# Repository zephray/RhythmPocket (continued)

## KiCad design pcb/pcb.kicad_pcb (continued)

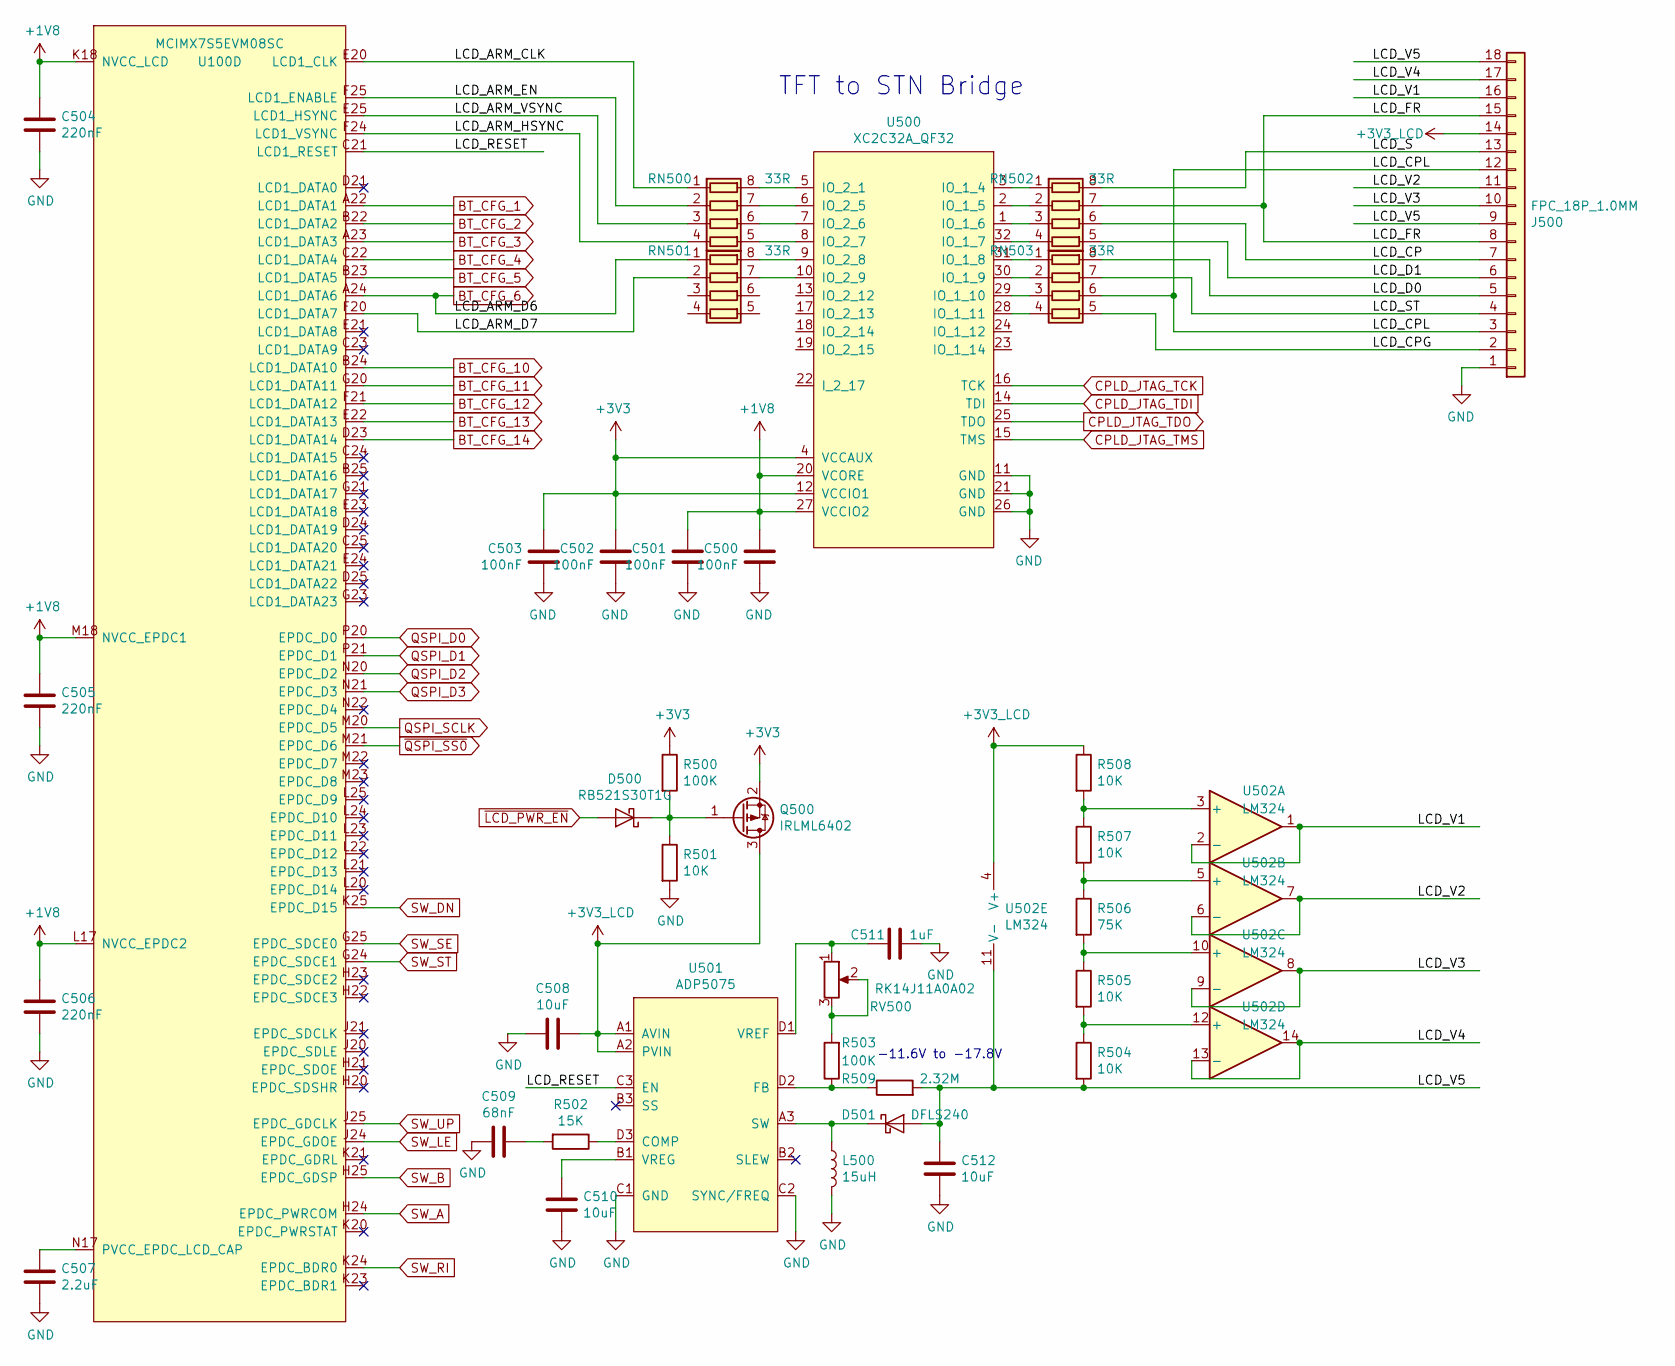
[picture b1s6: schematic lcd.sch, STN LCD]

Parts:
C500, C501, C502, C503: 100nF; C_0402_1005Metric
C504, C505, C506: 220nF; C_0402_1005Metric
C507: 2.2uF; C_0402_1005Metric
C508, C510, C512: 10uF; C_0603_1608Metric
C509: 68nF; C_0402_1005Metric
C511: 1uF; C_0402_1005Metric
D500: RB521S30T1G; D_SOD-523
D501: DFLS240; D_SOD-123
J500: FPC_18P_1.0MM; TE_1-84953-8_1x18-1MP_P1.0mm_Horizontal
L500: 15uH; L_Vishay_IHLP-1212
Q500: IRLML6402; SOT-23
R500, R503: 100K; R_0603_1608Metric
R501, R504, R505, R507, R508: 10K; R_0603_1608Metric
R502: 15K; R_0603_1608Metric
R506: 75K; R_0603_1608Metric
R509: 2.32M; R_0603_1608Metric
RN500, RN501, RN502, RN503: 33R; R_Array_Convex_4x0402
RV500: RK14J11A0A02; Potentiometer_RK14J
U100: MCIMX7S5EVM08SC; BGA-541_25x25_19.0x19.0mm
U500: XC2C32A_QF32; QFN-32-1EP_5x5mm_P0.5mm_EP3.1x3.1mm
U501: ADP5075; WLCSP-12_3x4
U502: LM324; SOIC-16_3.9x9.9mm_P1.27mm

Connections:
+1V8: C500.1, C501.1, C504.1, C505.1, C506.1, U100.K18 (NVCC_LCD), U100.L17 (NVCC_EPDC2), U100.M18 (NVCC_EPDC1), U500.20 (VCORE), U500.27 (VCCIO2); also elsewhere on the board
+3V3: C502.1, C503.1, Q500.2 (S), R500.1, U500.4 (VCCAUX), U500.12 (VCCIO1); also elsewhere on the board
+3V3_LCD: C508.1, J500.14, Q500.3 (D), R508.1, U501.A1 (AVIN), U501.A2 (PVIN), U502.4 (V+)
/lcd/LCD_ARM_CLK: RN500.1 (R1.1), U100.E20 (LCD1_CLK)
/lcd/LCD_ARM_D7: RN501.2 (R2.1), U100.F20 (LCD1_DATA7)
/lcd/LCD_ARM_EN: RN500.2 (R2.1), U100.F25 (LCD1_ENABLE)
/lcd/LCD_ARM_HSYNC: RN500.4 (R4.1), U100.F24 (LCD1_VSYNC)
/lcd/LCD_ARM_VSYNC: RN500.3 (R3.1), U100.E25 (LCD1_HSYNC)
/lcd/LCD_CP: J500.7, RN502.6 (R3.2)
/lcd/LCD_CPG: J500.2, RN503.5 (R4.2)
/lcd/LCD_CPL: J500.3, J500.12, RN503.6 (R3.2)
/lcd/LCD_D0: J500.5, RN503.8 (R1.2)
/lcd/LCD_D1: J500.6, RN502.5 (R4.2)
/lcd/LCD_FR: J500.8, J500.15, RN502.7 (R2.2)
/lcd/LCD_RESET: U100.C21 (LCD1_RESET), U501.C3 (EN)
/lcd/LCD_S: J500.13, RN502.8 (R1.2)
/lcd/LCD_ST: J500.4, RN503.7 (R2.2)
/lcd/LCD_V1: J500.16, U502.1, U502.2 (-)
/lcd/LCD_V2: J500.11, U502.6 (-), U502.7
/lcd/LCD_V3: J500.10, U502.8, U502.9 (-)
/lcd/LCD_V4: J500.17, U502.13 (-), U502.14
/lcd/LCD_V5: C512.2, D501.2 (A), J500.9, J500.18, R504.2, R509.2, U502.11 (V-)
BT_CFG_1: U100.A22 (LCD1_DATA1); also elsewhere on the board
BT_CFG_2: U100.B22 (LCD1_DATA2); also elsewhere on the board
BT_CFG_3: U100.A23 (LCD1_DATA3); also elsewhere on the board
BT_CFG_4: U100.C22 (LCD1_DATA4); also elsewhere on the board
BT_CFG_5: U100.B23 (LCD1_DATA5); also elsewhere on the board
BT_CFG_6: RN501.1 (R1.1), U100.A24 (LCD1_DATA6); also elsewhere on the board
BT_CFG_10: U100.B24 (LCD1_DATA10); also elsewhere on the board
BT_CFG_11: U100.G20 (LCD1_DATA11); also elsewhere on the board
BT_CFG_12: U100.F21 (LCD1_DATA12); also elsewhere on the board
BT_CFG_13: U100.E22 (LCD1_DATA13); also elsewhere on the board
BT_CFG_14: U100.D23 (LCD1_DATA14); also elsewhere on the board
CPLD_JTAG_TCK: U500.16 (TCK); also elsewhere on the board
CPLD_JTAG_TDI: U500.14 (TDI); also elsewhere on the board
CPLD_JTAG_TDO: U500.25 (TDO); also elsewhere on the board
CPLD_JTAG_TMS: U500.15 (TMS); also elsewhere on the board
GND: C500.2, C501.2, C502.2, C503.2, C504.2, C505.2, C506.2, C507.2, C508.2, C509.2, C510.2, C511.1, C512.1, J500.1, L500.2, R501.2, U500.11 (GND), U500.21 (GND), U500.26 (GND), U501.C1 (GND), U501.C2 (SYNC/FREQ); also elsewhere on the board
unnamed: C507.1, U100.N17 (PVCC_EPDC_LCD_CAP)
unnamed: C509.1, R502.2
unnamed: C510.1, U501.B1 (VREG)
unnamed: C511.2, RV500.1, U501.D1 (VREF)
unnamed: D500.1 (K), Q500.1 (G), R500.2, R501.1
unnamed: D501.1 (K), L500.1, U501.A3 (SW)
unnamed: R502.1, U501.D3 (COMP)
unnamed: R503.1, R509.1, U501.D2 (FB)
unnamed: R503.2, RV500.2, RV500.3
unnamed: R504.1, R505.2, U502.12 (+)
unnamed: R505.1, R506.2, U502.10 (+)
unnamed: R506.1, R507.2, U502.5 (+)
unnamed: R507.1, R508.2, U502.3 (+)
unnamed: RN500.5 (R4.2), U500.8 (IO_2_7)
unnamed: RN500.6 (R3.2), U500.7 (IO_2_6)
unnamed: RN500.7 (R2.2), U500.6 (IO_2_5)
unnamed: RN500.8 (R1.2), U500.5 (IO_2_1)
unnamed: RN501.7 (R2.2), U500.10 (IO_2_9)
unnamed: RN501.8 (R1.2), U500.9 (IO_2_8)
unnamed: RN502.1 (R1.1), U500.3 (IO_1_4)
unnamed: RN502.2 (R2.1), U500.2 (IO_1_5)
unnamed: RN502.3 (R3.1), U500.1 (IO_1_6)
unnamed: RN502.4 (R4.1), U500.32 (IO_1_7)
unnamed: RN503.1 (R1.1), U500.31 (IO_1_8)
unnamed: RN503.2 (R2.1), U500.30 (IO_1_9)
unnamed: RN503.3 (R3.1), U500.29 (IO_1_10)
unnamed: RN503.4 (R4.1), U500.28 (IO_1_11)
QSPI_D0: U100.P20 (EPDC_D0); also elsewhere on the board
QSPI_D1: U100.P21 (EPDC_D1); also elsewhere on the board
QSPI_D2: U100.N20 (EPDC_D2); also elsewhere on the board
QSPI_D3: U100.N21 (EPDC_D3); also elsewhere on the board
QSPI_SCLK: U100.M20 (EPDC_D5); also elsewhere on the board
SW_A: U100.H24 (EPDC_PWRCOM); also elsewhere on the board
SW_B: U100.H25 (EPDC_GDSP); also elsewhere on the board
SW_DN: U100.K25 (EPDC_D15); also elsewhere on the board
SW_LE: U100.J24 (EPDC_GDOE); also elsewhere on the board
SW_RI: U100.K24 (EPDC_BDR0); also elsewhere on the board
SW_SE: U100.G25 (EPDC_SDCE0); also elsewhere on the board
SW_ST: U100.G24 (EPDC_SDCE1); also elsewhere on the board
SW_UP: U100.J25 (EPDC_GDCLK); also elsewhere on the board
~LCD_PWR_EN: D500.2 (A); also elsewhere on the board
~QSPI_SS0: U100.M21 (EPDC_D6); also elsewhere on the board

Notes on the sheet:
TFT to STN Bridge
-11.6V to -17.8V

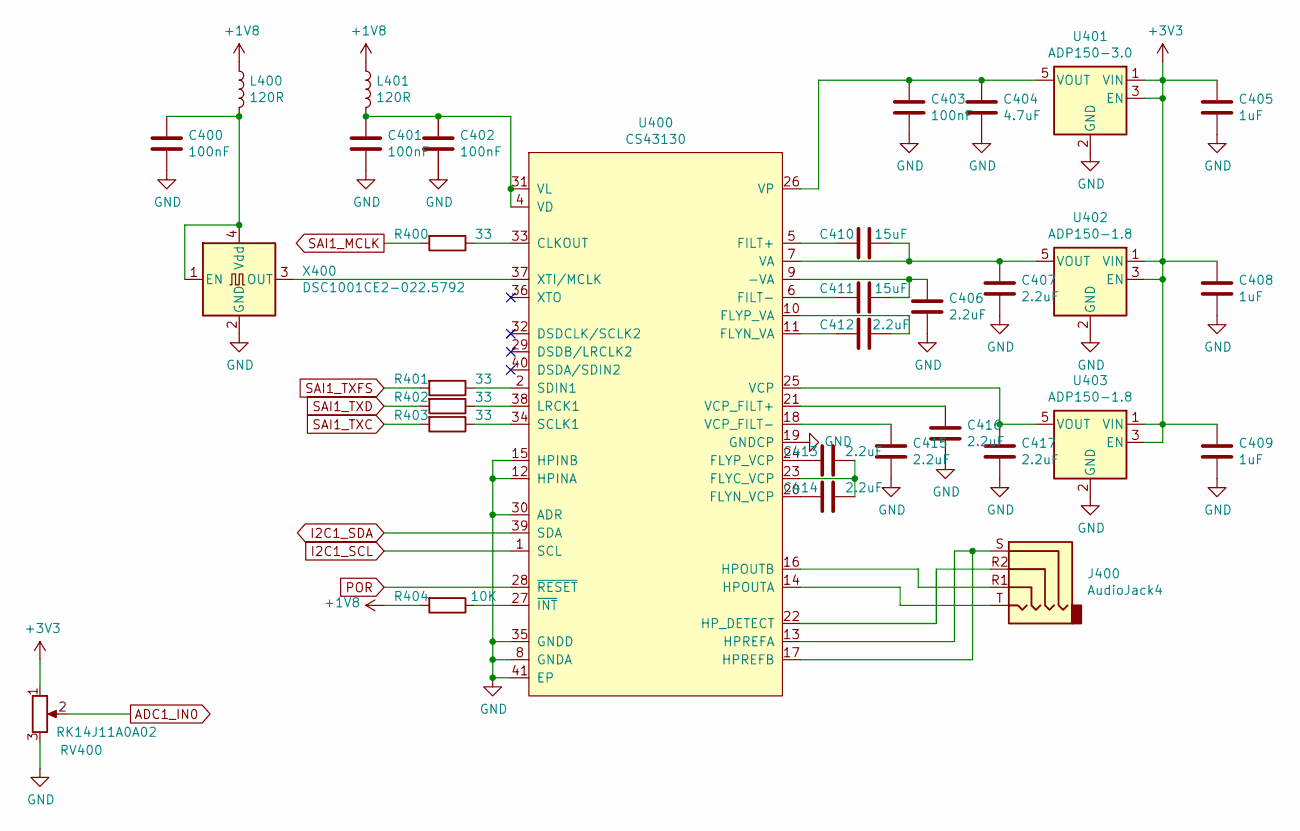
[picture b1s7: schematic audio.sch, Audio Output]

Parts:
C400, C401, C402, C403: 100nF; C_0402_1005Metric
C404: 4.7uF; C_0603_1608Metric
C405, C408, C409: 1uF; C_0402_1005Metric
C406, C407, C412, C413, C414, C415, C416, C417: 2.2uF; C_0402_1005Metric
C410, C411: 15uF; C_0603_1608Metric
J400: AudioJack4; Jack_3.5mm_PJ320D_Horizontal
L400, L401: 120R; L_0603_1608Metric
R400, R401, R402, R403: 33; R_0603_1608Metric
R404: 10K; R_0603_1608Metric
RV400: RK14J11A0A02; Potentiometer_RK14J
U400: CS43130; QFN-40-1EP_5x5mm_P0.4mm_EP3.6x3.6mm_ThermalVias
U401: ADP150-3.0; SOT-23-5
U402, U403: ADP150-1.8; SOT-23-5
X400: DSC1001CE2-022.5792; Oscillator_SMD_Abracon_ASE-4Pin_3.2x2.5mm

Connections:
+1V8: L400.1, L401.1, R404.2; also elsewhere on the board
+3V3: C405.1, C408.1, C409.1, RV400.1, U401.1 (VIN), U401.3 (EN), U402.1 (VIN), U402.3 (EN), U403.1 (VIN), U403.3 (EN); also elsewhere on the board
ADC1_IN0: RV400.2; also elsewhere on the board
GND: C400.2, C401.2, C402.2, C403.2, C404.2, C405.2, C406.2, C407.2, C408.2, C409.2, C415.2, C416.2, C417.2, RV400.3, U400.8 (GNDA), U400.12 (HPINA), U400.15 (HPINB), U400.19 (GNDCP), U400.30 (ADR), U400.35 (GNDD), U400.41 (EP), U401.2 (GND), U402.2 (GND), U403.2 (GND), X400.2 (GND); also elsewhere on the board
I2C1_SCL: U400.1 (SCL); also elsewhere on the board
I2C1_SDA: U400.39 (SDA); also elsewhere on the board
unnamed: C400.1, L400.2, X400.1 (EN), X400.4 (Vdd)
unnamed: C401.1, C402.1, L401.2, U400.4 (VD), U400.31 (VL)
unnamed: C403.1, C404.1, U400.26 (VP), U401.5 (VOUT)
unnamed: C406.1, C411.1, U400.9 (-VA)
unnamed: C407.1, C410.1, U400.7 (VA), U402.5 (VOUT)
unnamed: C410.2, U400.5 (FILT+)
unnamed: C411.2, U400.6 (FILT-)
unnamed: C412.1, U400.10 (FLYP_VA)
unnamed: C412.2, U400.11 (FLYN_VA)
unnamed: C413.1, C414.1, U400.23 (FLYC_VCP)
unnamed: C413.2, U400.24 (FLYP_VCP)
unnamed: C414.2, U400.20 (FLYN_VCP)
unnamed: C415.1, U400.18 (VCP_FILT-)
unnamed: C416.1, U400.21 (VCP_FILT+)
unnamed: C417.1, U400.25 (VCP), U403.5 (VOUT)
unnamed: J400.R1, U400.16 (HPOUTB)
unnamed: J400.R2, U400.22 (HP_DETECT)
unnamed: J400.S, U400.13 (HPREFA), U400.17 (HPREFB)
unnamed: J400.T, U400.14 (HPOUTA)
unnamed: R400.1, U400.33 (CLKOUT)
unnamed: R401.1, U400.2 (SDIN1)
unnamed: R402.1, U400.38 (LRCK1)
unnamed: R403.1, U400.34 (SCLK1)
unnamed: R404.1, U400.27 (~INT)
unnamed: U400.37 (XTI/MCLK), X400.3 (OUT)
POR: U400.28 (~RESET); also elsewhere on the board
SAI1_MCLK: R400.2; also elsewhere on the board
SAI1_TXC: R403.2; also elsewhere on the board
SAI1_TXD: R402.2; also elsewhere on the board
SAI1_TXFS: R401.2; also elsewhere on the board

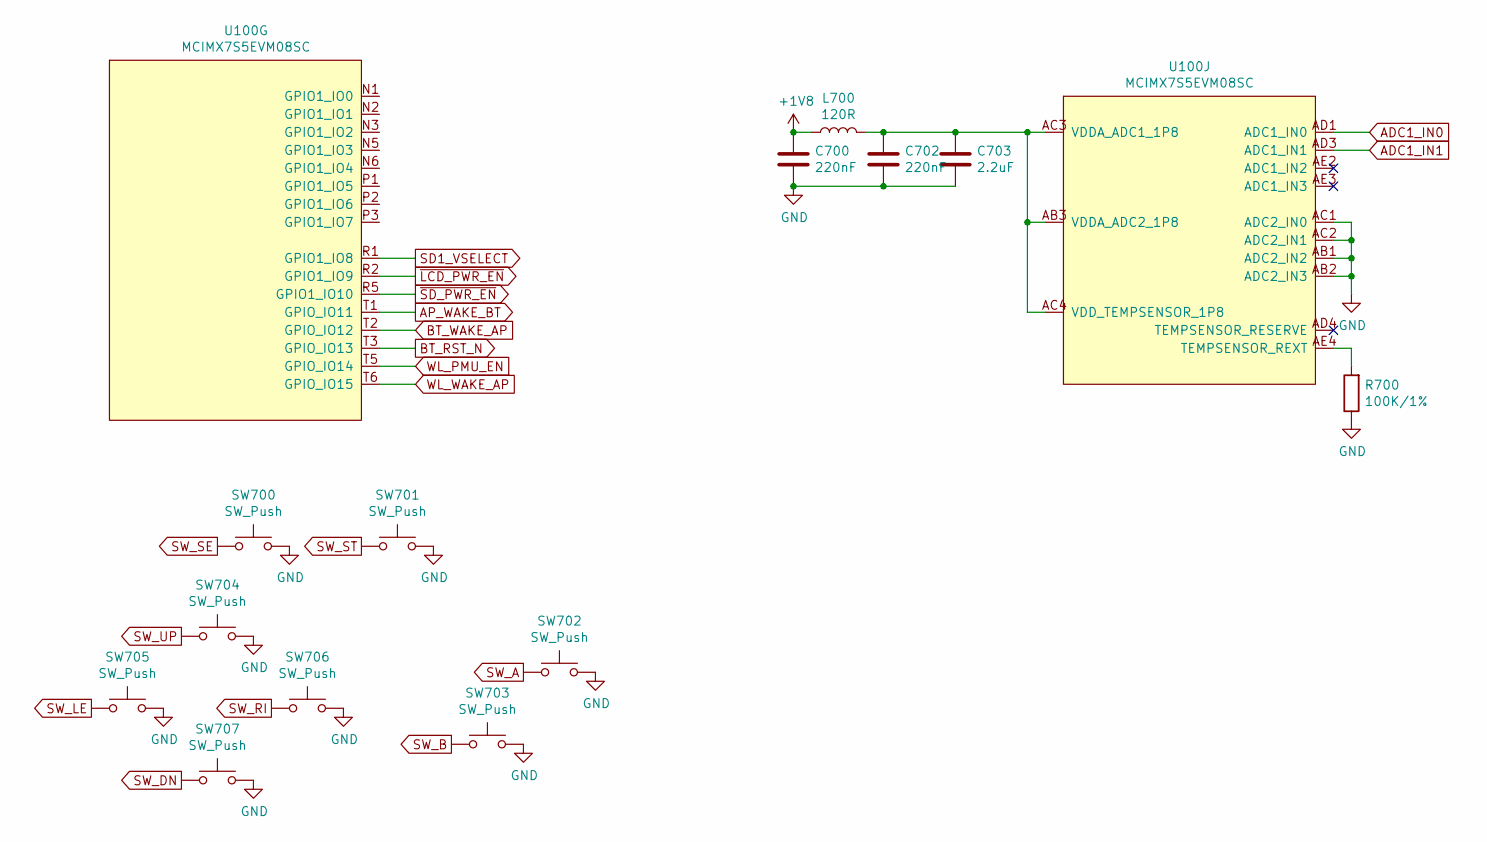
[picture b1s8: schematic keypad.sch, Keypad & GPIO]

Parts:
C700, C702: 220nF; C_0402_1005Metric
C703: 2.2uF; C_0402_1005Metric
L700: 120R; L_0603_1608Metric
R700: 100K/1%; R_0603_1608Metric
SW700, SW701, SW702, SW703, SW704, SW705, SW706, SW707: SW_Push; contact
U100: MCIMX7S5EVM08SC; BGA-541_25x25_19.0x19.0mm

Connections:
+1V8: C700.1, L700.1; also elsewhere on the board
ADC1_IN0: U100.AD1 (ADC1_IN0); also elsewhere on the board
ADC1_IN1: U100.AD3 (ADC1_IN1); also elsewhere on the board
AP_WAKE_BT: U100.T1 (GPIO_IO11); also elsewhere on the board
BT_RST_N: U100.T3 (GPIO_IO13); also elsewhere on the board
BT_WAKE_AP: U100.T2 (GPIO_IO12); also elsewhere on the board
GND: C700.2, C702.2, C703.2, R700.1, SW700.2, SW701.2, SW702.2, SW703.2, SW704.2, SW705.2, SW706.2, SW707.2, U100.AB1 (ADC2_IN2), U100.AB2 (ADC2_IN3), U100.AC1 (ADC2_IN0), U100.AC2 (ADC2_IN1); also elsewhere on the board
unnamed: C702.1, C703.1, L700.2, U100.AB3 (VDDA_ADC2_1P8), U100.AC3 (VDDA_ADC1_1P8), U100.AC4 (VDD_TEMPSENSOR_1P8)
unnamed: R700.2, U100.AE4 (TEMPSENSOR_REXT)
SD1_VSELECT: U100.R1 (GPIO1_IO8); also elsewhere on the board
SW_A: SW702.1; also elsewhere on the board
SW_B: SW703.1; also elsewhere on the board
SW_DN: SW707.1; also elsewhere on the board
SW_LE: SW705.1; also elsewhere on the board
SW_RI: SW706.1; also elsewhere on the board
SW_SE: SW700.1; also elsewhere on the board
SW_ST: SW701.1; also elsewhere on the board
SW_UP: SW704.1; also elsewhere on the board
WL_PMU_EN: U100.T5 (GPIO_IO14); also elsewhere on the board
WL_WAKE_AP: U100.T6 (GPIO_IO15); also elsewhere on the board
~LCD_PWR_EN: U100.R2 (GPIO1_IO9); also elsewhere on the board
~SD_PWR_EN: U100.R5 (GPIO1_IO10); also elsewhere on the board

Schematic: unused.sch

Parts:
U100: MCIMX7S5EVM08SC; BGA-541_25x25_19.0x19.0mm

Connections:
GND: U100.AA13 (PCIE_REXT), U100.H16 (NVCC_ENET1); also elsewhere on the board

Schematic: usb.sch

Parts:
C600: 10uF; C_0603_1608Metric
C601, C602, C604, C605: 220nF; C_0402_1005Metric
C603, C606: 2.2uF; C_0402_1005Metric
C607: 100nF; C_0805_2012Metric
D600, D601: B72590D0050H160; D_0402_1005Metric
J600: USB_B_Micro; USB_Micro-B_Amphenol_10103594-0001LF_Horizontal
J601: USB_A; USB_A_Stewart_SS-52100-001_Horizontal
R600: 0; R_0805_2012Metric
R601, R602, R606, R607: 22; R_0603_1608Metric
R603, R604: 200/1%; R_0603_1608Metric
R605: 47K; R_0603_1608Metric
R608: 1R; R_0603_1608Metric
U100: MCIMX7S5EVM08SC; BGA-541_25x25_19.0x19.0mm
U600: USBLC6-2SC6; SOT-23-6

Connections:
+3V3: C601.1, C604.1, R605.2, U100.F9 (VDD_USB_OTG2_3P3_IN), U100.F10 (VDD_USB_OTG1_3P3_IN); also elsewhere on the board
GND: C601.2, C602.2, C603.2, C604.2, C605.2, C606.2, C607.2, D600.2 (A2), D601.2 (A2), J601.4 (GND), J601.5 (Shield), R600.2, R603.2, R604.2, R608.2, U600.2 (GND); also elsewhere on the board
unnamed: C600.2, R608.1
unnamed: C602.1, C603.1, U100.H10 (VDD_USB_OTG1_1P0_CAP)
unnamed: C605.1, C606.1, U100.J11 (VDD_USB_OTG2_1P0_CAP)
unnamed: C607.1, J600.5 (GND), J600.6 (Shield), R600.1
unnamed: D600.1 (A1), J600.4 (ID), U100.B7 (USB_OTG1_ID)
unnamed: J600.2 (D-), R602.2, U600.1 (IO1), U600.6 (IO1)
unnamed: J600.3 (D+), R601.2, U600.3 (IO2), U600.4 (IO2)
unnamed: J601.2 (D-), R607.2
unnamed: J601.3 (D+), R606.2
unnamed: R601.1, U100.B8 (USB_OTG1_DP)
unnamed: R602.1, U100.A8 (USB_OTG1_DN)
unnamed: R603.1, U100.A7 (USB1_OTG1_REXT)
unnamed: R604.1, U100.A11 (USB_OTG2_REXT)
unnamed: R605.1, U100.C7 (~USB_OTG1_CHD)
unnamed: R606.1, U100.B10 (USB_OTG2_DP)
unnamed: R607.1, U100.A10 (USB_OTG2_DN)
VBUS: C600.1, D601.1 (A1), J600.1 (VBUS), J601.1 (VBUS), U100.C8 (USB_OTG1_VBUS), U100.C10 (USB2_VBUS); also elsewhere on the board

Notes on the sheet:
The Type A port is not ESD protected, and only powered if Type B Micro is connected (shared power). This port is meant for development purpose only.

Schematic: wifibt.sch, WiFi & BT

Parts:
ANT800: PCB_WIFI_ANT; bt_antenna_1ant_2gnd
C800, C802: 100nF; C_0402_1005Metric
C801, C803: 10uF; C_0603_1608Metric
C804: 33pF/50V/5%; C_0402_1005Metric
C805, C806: DNP; C_0402_1005Metric
D800: RB521S30T1G; D_SOD-523
Q800: IRLML6402; SOT-23
R800: 100K; R_0603_1608Metric
R801, R803: 10K; R_0603_1608Metric
R802: 0R; R_0603_1608Metric
U800: RTL8723BS; RL-SM02BD(RTL8723BS)

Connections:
+3V3: Q800.2 (S), R800.1; also elsewhere on the board
AP_WAKE_BT: U800.6 (BT_WAKE); also elsewhere on the board
BT_RST_N: U800.34 (BT_DIS#); also elsewhere on the board
BT_WAKE_AP: U800.7 (BT_HOST_WAKE); also elsewhere on the board
CCM_CLKO2: R803.2, U800.24 (SUSCLK_IN/GPIO6); also elsewhere on the board
GND: ANT800.2, C800.2, C801.2, C802.2, C803.2, C805.1, C806.1, R801.2, U800.1 (GND), U800.20 (GND), U800.31 (GND), U800.33 (GND), U800.36 (GND), U800.41 (GND); also elsewhere on the board
unnamed: ANT800.1, C806.2, R802.2
unnamed: C800.1, C801.1, C802.1, C803.1, Q800.3 (D), R803.1, U800.9 (VDD33), U800.22 (VDD_IO)
unnamed: C804.1, U800.2 (WIFI/BT_ANT)
unnamed: C804.2, C805.2, R802.1
unnamed: D800.1 (K), Q800.1 (G), R800.2, R801.1
SD2_CLK: U800.17 (SD_CLK); also elsewhere on the board
SD2_CMD: U800.16 (SD_CMD); also elsewhere on the board
SD2_DATA0: U800.18 (SD_D0); also elsewhere on the board
SD2_DATA1: U800.19 (SD_D1); also elsewhere on the board
SD2_DATA2: U800.14 (SD_D2); also elsewhere on the board
SD2_DATA3: U800.15 (SD_D3); also elsewhere on the board
UART3_RTS: U800.44 (UART_CTS); also elsewhere on the board
UART3_RXD: U800.42 (UART_OUT); also elsewhere on the board
UART3_TXD: U800.43 (UART_IN); also elsewhere on the board
WL_PMU_EN: U800.12 (WL_DSI#/GPIO9); also elsewhere on the board
WL_WAKE_AP: U800.13 (WL_HOST_WAKE); also elsewhere on the board

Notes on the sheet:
Due to I/O voltage constraint, headset profile would not be supported. Use A2DP instead.

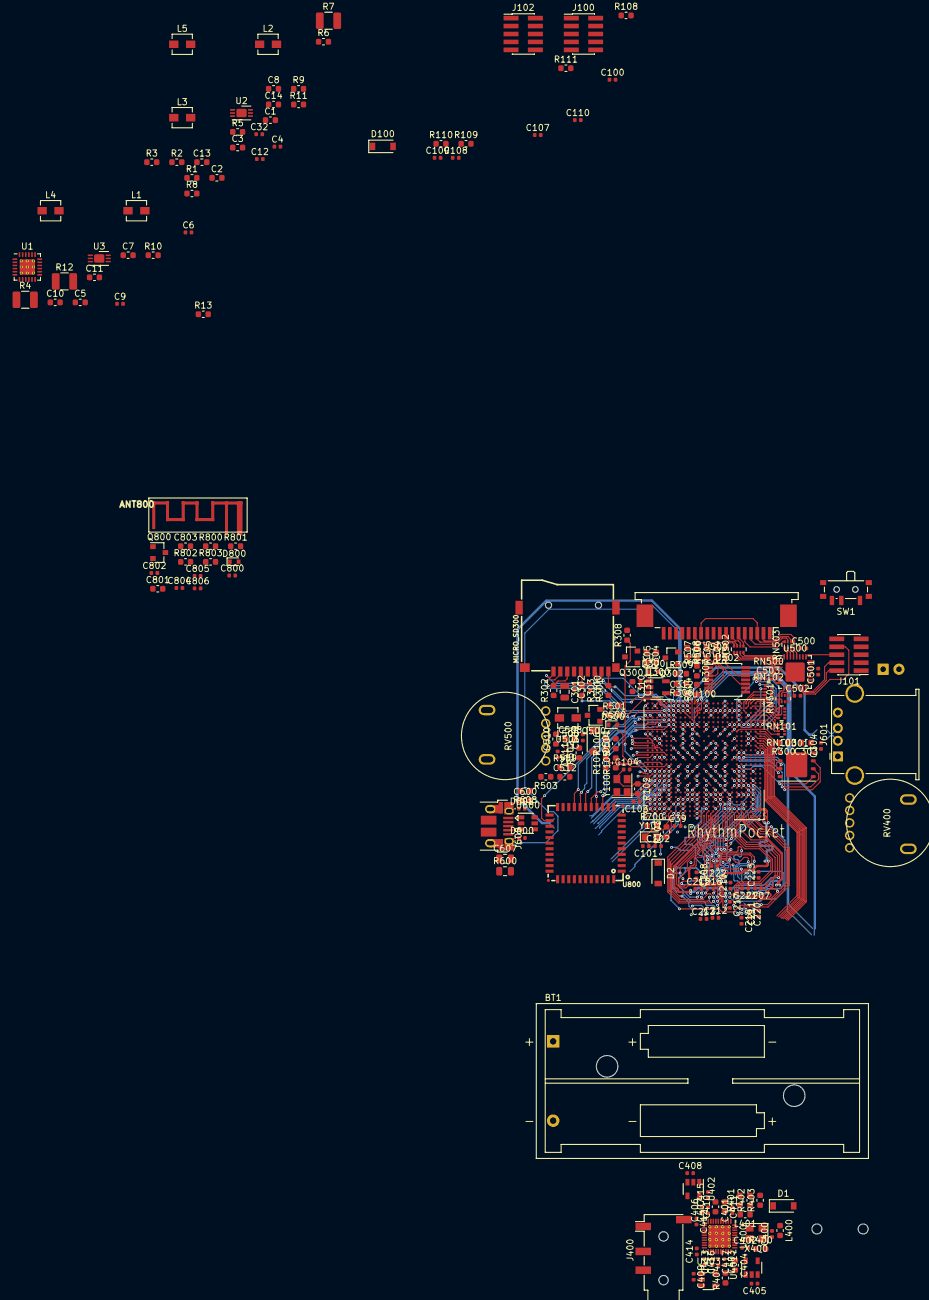
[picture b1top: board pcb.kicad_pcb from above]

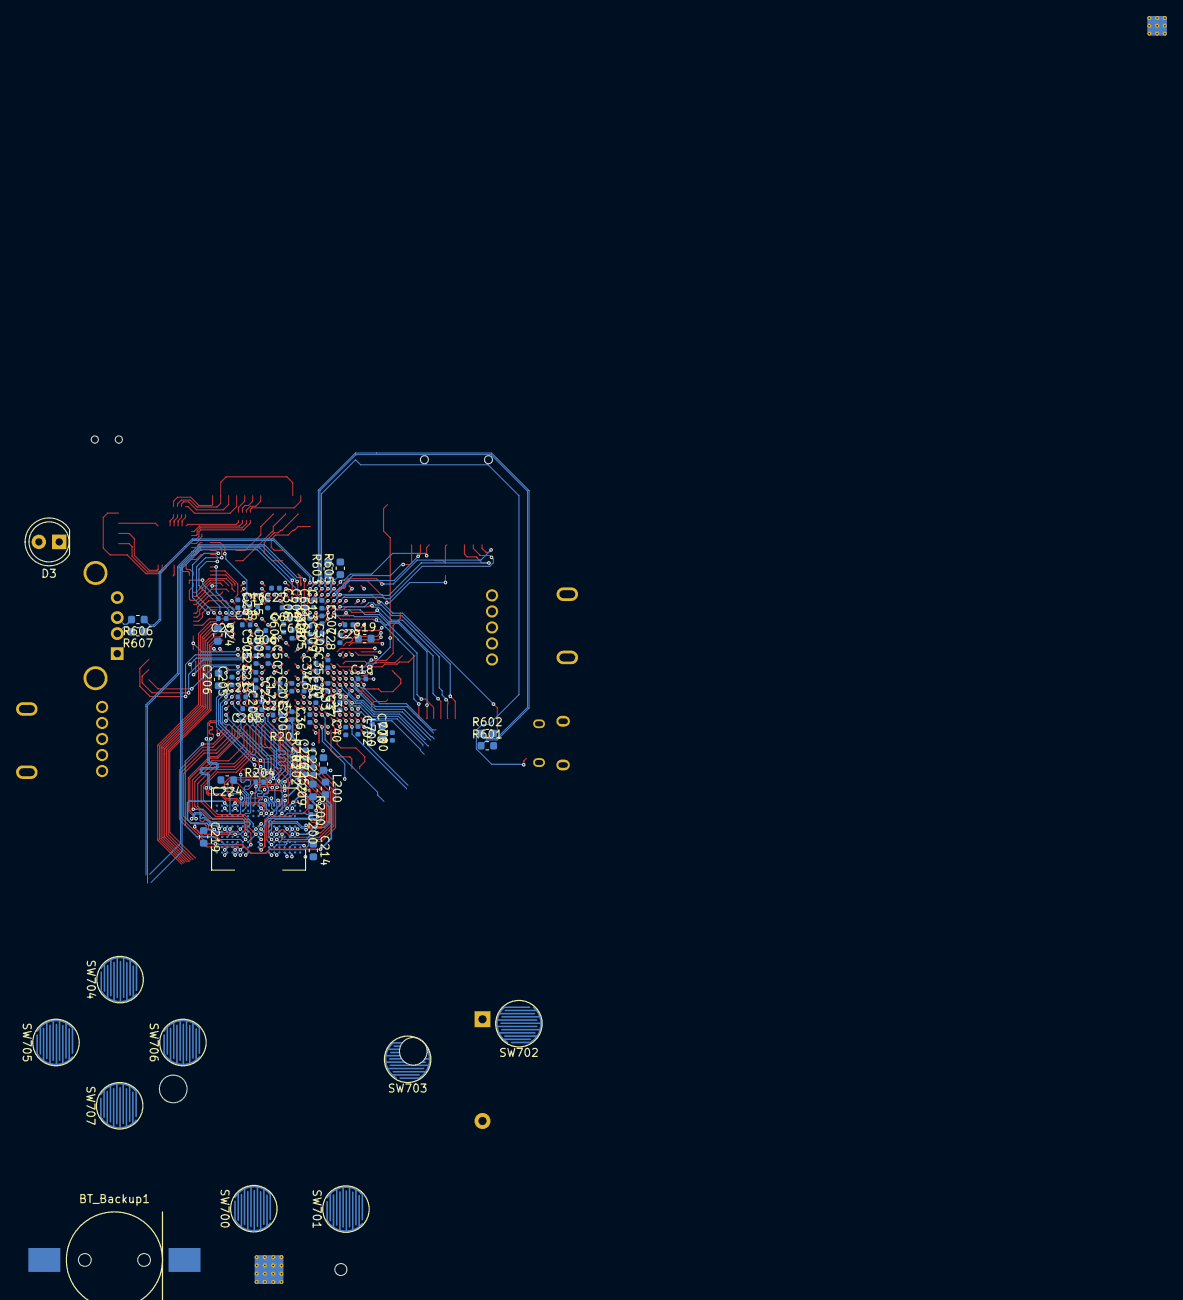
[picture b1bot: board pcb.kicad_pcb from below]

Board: 4 copper layers, 281 parts (83 on the bottom side), 256 nets.

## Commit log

2019-06-30 pcb: symbol for imx, ddr, and dac
2019-06-30 pcb: ddr schematics
2019-06-30 pcb: draw ltc3456 symbol
2019-07-01 pcb: working on storage sch
2019-07-01 pcb: working on sch
2019-07-02 pcb: draw sch for wifi & bt
2019-07-03 pcb: finishing sch for r0.1
2019-07-03 pcb: initial netlist
2019-07-05 pcb: working on ddr
2019-07-05 pcb: layout lpddr2
2019-07-07 pcb: working on layout
2019-07-09 pcb: add board outline
2019-07-16 pcb: routing
2019-07-17 pcb: rev 0.1
2019-08-09 pcb: update kicad version
2019-08-09 pcb: remap schematic symbols
2019-08-11 pcb: bug fixes
2019-08-11 fix #2
2019-08-14 pcb: rev 0.2
2019-08-31 misc: upload lpddr2 init script
2019-08-31 pcb: update pcb revision number
2019-09-01 misc: add 533 configuration
